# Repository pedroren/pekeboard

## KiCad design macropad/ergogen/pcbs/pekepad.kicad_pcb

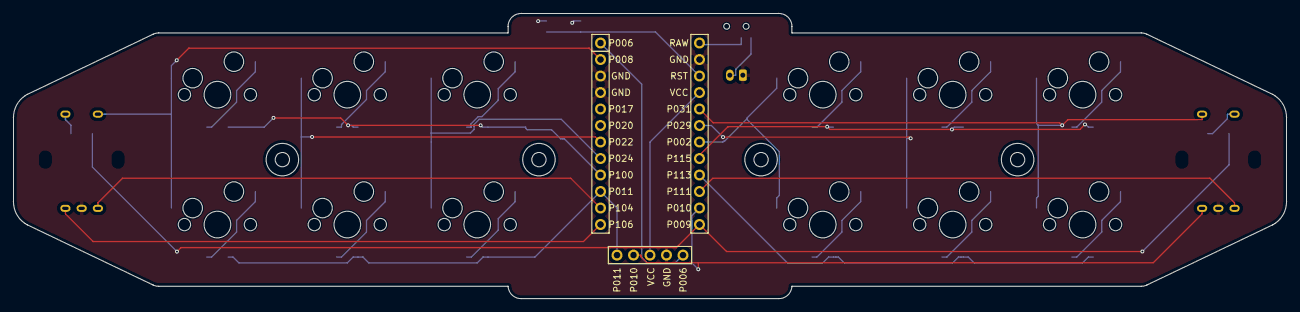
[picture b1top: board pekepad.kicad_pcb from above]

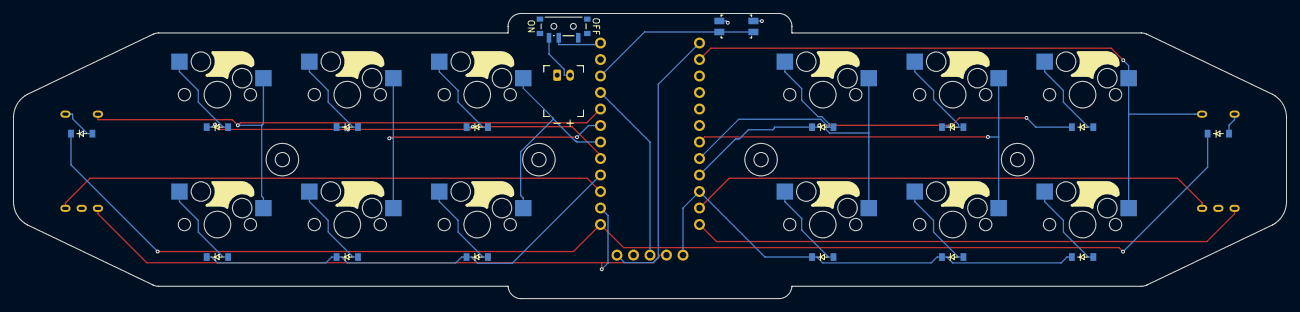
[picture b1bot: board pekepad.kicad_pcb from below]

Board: 2 copper layers, 196.0 x 43.9 mm, 37 parts (29 on the bottom side), 35 nets.

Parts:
D1, D2, D3, D4, D5, D6, D7, D8, D9, D10, D11, D12, D13, D14: diode_tht_sod123
DISP1: display_nice_view
JST1: battery_connector_jst_ph_2
MCU1: mcu_nice_nano
MH1, MH2, MH3, MH4: mounting_hole_npth
PWR1: power_switch_smd_side
RE1, RE2: rotary_encoder_ec11_ec12
RST1: reset_switch_smd_side
S1, S2, S3, S4, S5, S6, S7, S8, S9, S10, S11, S12: switch_mx

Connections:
BAT_P: JST1.2, PWR1.3
GND: DISP1.4, JST1.1, MCU1.2, MCU1.21, MCU1.22, RE1.B, RE2.B, RST1.1, RST1.3
P002: MCU1.7, S11.1, S12.1
P006: DISP1.5, MCU1.24
P008: MCU1.23, RE1.S2, S1.1, S2.1
P009: D13.1, D14.1, MCU1.12
P010: DISP1.2, MCU1.11, RE2.C
P011: D1.1, D3.1, D5.1, DISP1.1, MCU1.15
P022: MCU1.18, S3.1, S4.1
P024: MCU1.17, S5.1, S6.1
P029: MCU1.6, S9.1, S10.1
P031: MCU1.5, RE2.S1, S7.1, S8.1
P100: D2.1, D4.1, D6.1, MCU1.16
P104: MCU1.14, RE1.A
P106: MCU1.13, RE1.C
P111: MCU1.10, RE2.A
P113: D7.1, D9.1, D11.1, MCU1.9
P115: D8.1, D10.1, D12.1, MCU1.8
RAW: MCU1.1, PWR1.2
RST: MCU1.3, RST1.2, RST1.4
VCC: DISP1.3, MCU1.4
enccol_encrow: D13.2, RE1.S1
inner_bottom: D5.2, S5.2
inner_top: D6.2, S6.2
middle_bottom: D3.2, S3.2
middle_top: D4.2, S4.2
mirror_enccol_encrow: D14.2, RE2.S2
mirror_inner_bottom: D11.2, S11.2
mirror_inner_top: D12.2, S12.2
mirror_middle_bottom: D9.2, S9.2
mirror_middle_top: D10.2, S10.2
mirror_outer_bottom: D7.2, S7.2
mirror_outer_top: D8.2, S8.2
outer_bottom: D1.2, S1.2
outer_top: D2.2, S2.2
